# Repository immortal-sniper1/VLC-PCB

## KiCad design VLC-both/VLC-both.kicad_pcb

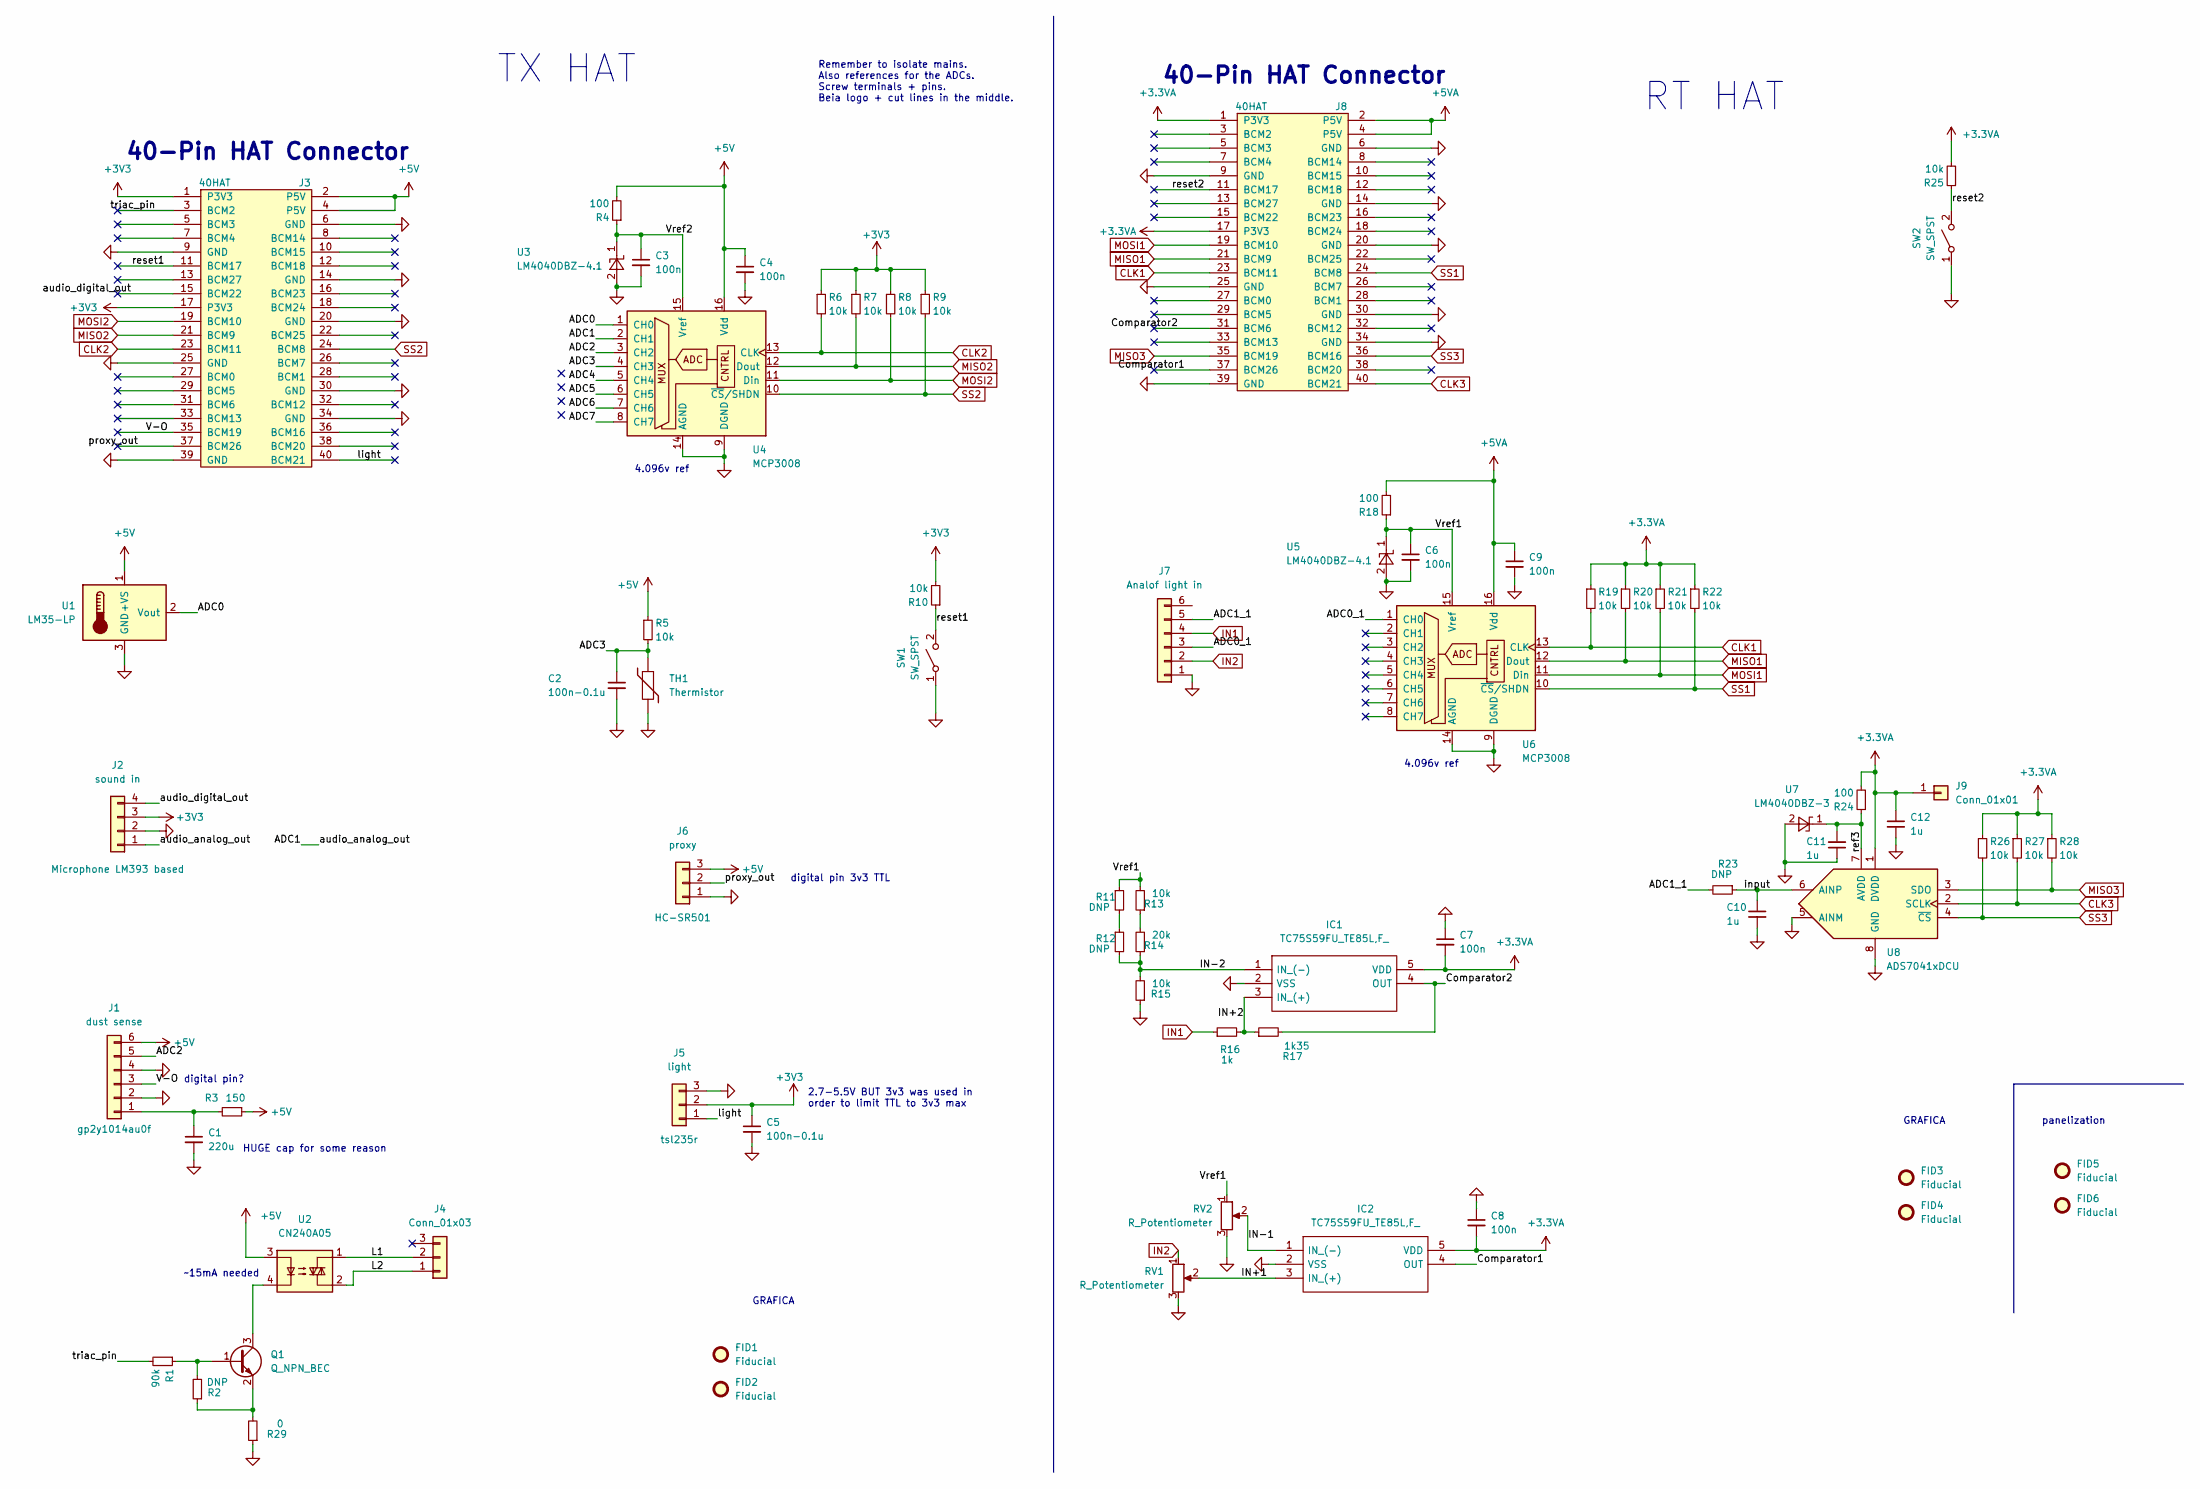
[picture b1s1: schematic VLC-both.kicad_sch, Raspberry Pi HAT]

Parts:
C1: 220u; CP_Elec_6.3x7.7
C2, C5: 100n-0.1u; C_0805_2012Metric
C3, C4, C6, C7, C8, C9: 100n; C_0805_2012Metric
C10, C11, C12: 1u; C_0805_2012Metric
FID1, FID3: Fiducial; Fiducial_0.5mm_Mask1mm
FID2, FID4: Fiducial; WEEE-Logo_4.2x6mm_SilkScreen
FID5, FID6: Fiducial; mouse bites 2.5mm wide 6mm long 0.6mm holes 0.3mm apart str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
IC1, IC2: TC75S59FU_TE85L,F_; TC75S59FUTE85LF; Mouser Part Number 757-TC75S59FUTE85LF
J1: dust sense; PinHeader_1x06_P2.54mm_Vertical
J2: sound in; PinHeader_1x04_P2.54mm_Vertical
J3, J8: 40HAT; PinSocket_2x20_P2.54mm_Vertical
J4: Conn_01x03; TerminalBlock_Altech_AK300-3_P5.00mm
J5: light; PinHeader_1x03_P2.54mm_Vertical
J6: proxy; PinHeader_1x03_P2.54mm_Vertical
J7: Analof light in; PinHeader_1x06_P2.54mm_Vertical
J9: Conn_01x01; PinHeader_1x01_P2.54mm_Vertical
Q1: Q_NPN_BEC; SOT-23
R1: 90k; R_0805_2012Metric
R2, R11, R12, R23: DNP; R_0805_2012Metric
R3: 150; R_0805_2012Metric
R4, R18, R24: 100; R_0805_2012Metric
R5, R6, R7, R8, R9, R10, R13, R15, R19, R20, R21, R22, R25, R26, R27, R28: 10k; R_0805_2012Metric
R14: 20k; R_0805_2012Metric
R16: 1k; R_0805_2012Metric
R17: 1k35; R_0805_2012Metric
R29: 0; R_0805_2012Metric
RV1, RV2: R_Potentiometer; Potentiometer_Piher_PT-6-V_Vertical
SW1, SW2: SW_SPST; PTS526SM15SMTR2LFS
TH1: Thermistor; PinHeader_1x02_P2.54mm_Vertical
U1: LM35-LP; PinHeader_1x03_P2.54mm_Vertical
U2: CN240A05; SIP4_Sharp-SSR_P7.62mm_Straight
U3, U5: LM4040DBZ-4.1; SOT-23
U4, U6: MCP3008; SOIC-16_3.9x9.9mm_P1.27mm
U7: LM4040DBZ-3; SOT-23
U8: ADS7041xDCU; VSSOP-8_2.3x2mm_P0.5mm

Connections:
+3.3VA: C7.2, C8.2, C12.1, IC1.5 (VDD), IC2.5 (VDD), J8.1 (P3V3), J8.17 (P3V3), J9.1, R19.1, R20.1, R21.1, R22.1, R24.2, R25.2, R26.1, R27.1, R28.1, U8.1 (DVDD)
+3V3: C5.1, J2.3, J3.1 (P3V3), J3.17 (P3V3), J5.2, R6.1, R7.1, R8.1, R9.1, R10.2
+5V: C4.1, J1.6, J3.2 (P5V), J3.4 (P5V), J6.3, R3.1, R4.2, R5.1, U1.1 (+VS), U2.3, U4.16 (Vdd)
+5VA: C9.1, J8.2 (P5V), J8.4 (P5V), R18.2, U6.16 (Vdd)
/ADC0: U1.2 (Vout), U4.1 (CH0)
/ADC0_1: J7.3, U6.1 (CH0)
/ADC1: J2.1, U4.2 (CH1)
/ADC1_1: J7.5, R23.2
/ADC2: J1.5, U4.3 (CH2)
/ADC3: C2.1, R5.2, TH1.1, U4.4 (CH3)
/ADC4: U4.5 (CH4)
/ADC5: U4.6 (CH5)
/ADC6: U4.7 (CH6)
/ADC7: U4.8 (CH7)
/Comparator1: IC2.4 (OUT), J8.37 (BCM26)
/Comparator2: IC1.4 (OUT), J8.31 (BCM6), R17.2
/IN+1: IC2.3 (IN_(+)), RV1.2
/IN+2: IC1.3 (IN_(+)), R16.2, R17.1
/IN-1: IC2.1 (IN_(-)), RV2.2
/IN-2: IC1.1 (IN_(-)), R12.2, R14.1, R15.2
/L1: J4.2, U2.1
/L2: J4.1, U2.2
/V-O: J1.3, J3.35 (BCM19)
/Vref1: C6.1, R11.1, R13.2, R18.1, RV2.1, U5.1 (K), U6.15 (Vref)
/Vref2: C3.1, R4.1, U3.1 (K), U4.15 (Vref)
/audio_digital_out: J2.4, J3.15 (BCM22)
/input: C10.1, R23.1, U8.6 (AINP)
/light: J3.40 (BCM21), J5.1
/proxy_out: J3.37 (BCM26), J6.2
/ref3: C11.2, R24.1, U7.1 (K), U8.7 (AVDD)
/reset1: J3.11 (BCM17), R10.1, SW1.2 (B)
/reset2: J8.11 (BCM17), R25.1, SW2.2 (B)
/triac_pin: J3.3 (BCM2), R1.2
CLK1: J8.23 (BCM11), R19.2, U6.13 (CLK)
CLK2: J3.23 (BCM11), R6.2, U4.13 (CLK)
CLK3: J8.40 (BCM21), R27.2, U8.2 (SCLK)
GND: C1.2, C2.2, C3.2, C4.2, C5.2, C6.2, C7.1, C8.1, C9.2, C10.2, C11.1, C12.2, IC1.2 (VSS), IC2.2 (VSS), J1.2, J1.4, J2.2, J3.6 (GND), J3.9 (GND), J3.14 (GND), J3.20 (GND), J3.25 (GND), J3.30 (GND), J3.34 (GND), J3.39 (GND), J5.3, J6.1, J7.1, J8.6 (GND), J8.9 (GND), J8.14 (GND), J8.20 (GND), J8.25 (GND), J8.30 (GND), J8.34 (GND), J8.39 (GND), R15.1, R29.1, RV1.3, RV2.3, SW1.1 (A), SW2.1 (A), TH1.2, U1.3 (GND), U3.2 (A), U4.9 (DGND), U4.14 (AGND), U5.2 (A), U6.9 (DGND), U6.14 (AGND), U7.2 (A), U8.5 (AINM), U8.8 (GND)
IN1: J7.4, R16.1
IN2: J7.2, RV1.1
MISO1: J8.21 (BCM9), R20.2, U6.12 (Dout)
MISO2: J3.21 (BCM9), R7.2, U4.12 (Dout)
MISO3: J8.35 (BCM19), R28.2, U8.3 (SDO)
MOSI1: J8.19 (BCM10), R21.2, U6.11 (Din)
MOSI2: J3.19 (BCM10), R8.2, U4.11 (Din)
unnamed: C1.1, J1.1, R3.2
unnamed: Q1.1 (B), R1.1, R2.2
unnamed: Q1.2 (E), R2.1, R29.2
unnamed: Q1.3 (C), U2.4
unnamed: R11.2, R12.1
unnamed: R13.1, R14.2
SS1: J8.24 (BCM8), R22.2, U6.10 (~CS/SHDN)
SS2: J3.24 (BCM8), R9.2, U4.10 (~CS/SHDN)
SS3: J8.36 (BCM16), R26.2, U8.4 (~CS)

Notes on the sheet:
4.096v ref
HUGE cap for some reason
Remember to isolate mains. Also references for the ADCs. Screw terminals + pins. Beia logo + cut lines in the middle.
40-Pin HAT Connector
~15mA needed
GRAFICA
RT HAT
2.7-5.5V BUT 3v3 was used in order to limit TTL to 3v3 max
digital pin?
digital pin 3v3 TTL
TX HAT
panelization

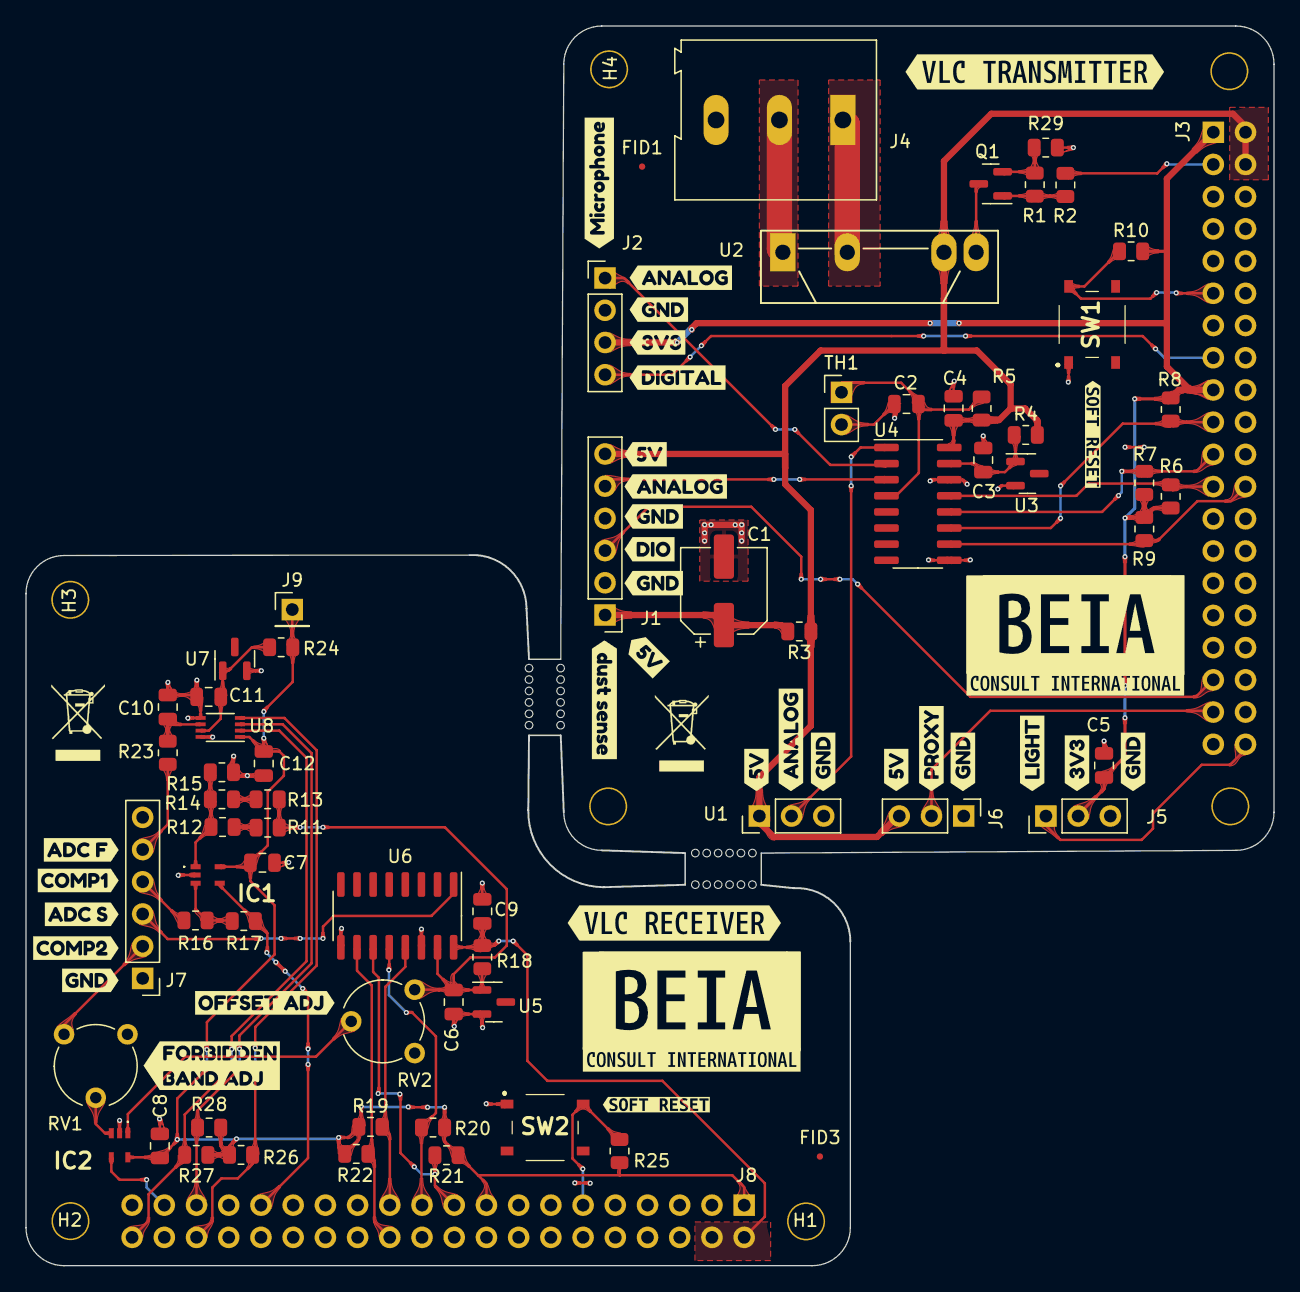
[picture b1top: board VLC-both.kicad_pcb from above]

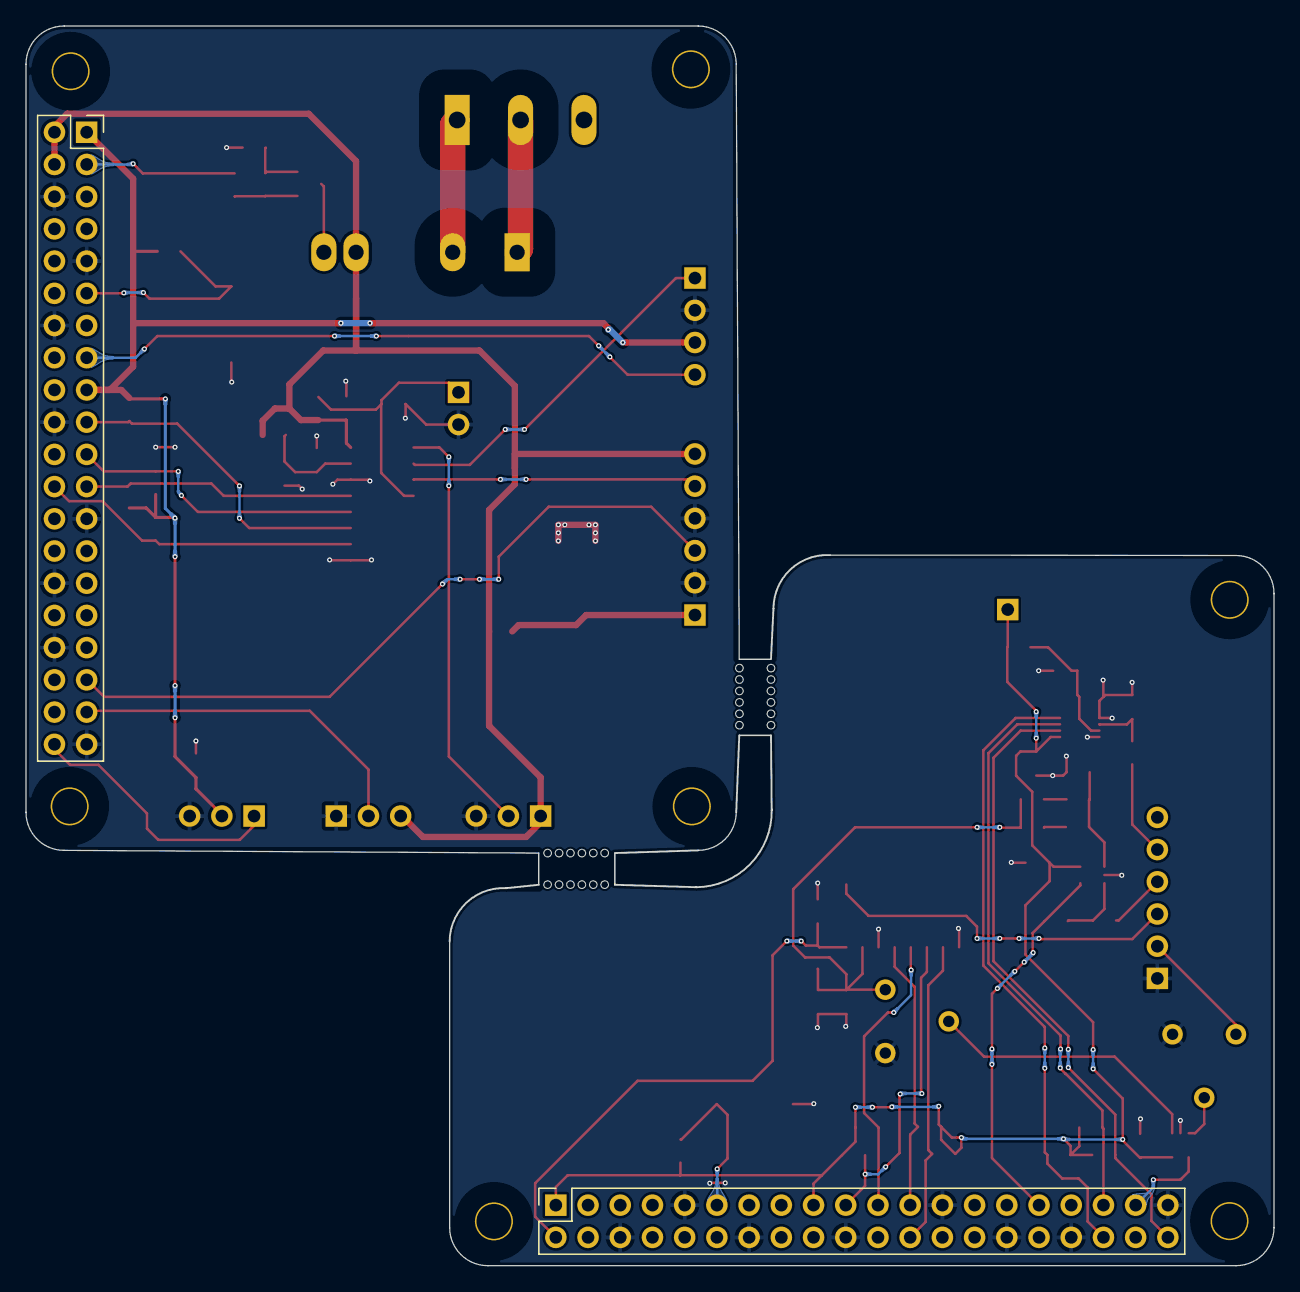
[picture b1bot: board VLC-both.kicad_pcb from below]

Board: 2 copper layers, 98.4 x 97.7 mm, 112 parts (2 on the bottom side), 49 nets.

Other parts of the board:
H1, H2, H3, H4: 3mm_Mounting_Hole; NPTH_3mm_ID
kibuzzard-62B5CDB9, kibuzzard-62B5CDB9#2: G***; kibuzzard-62B5CDB9
kibuzzard-62B56CEF, kibuzzard-62B56CEF#2, kibuzzard-62B56CEF#3, kibuzzard-62B56CEF#4: G***; kibuzzard-62B56CEF
kibuzzard-62B56DD8, kibuzzard-62B56DD8#2, kibuzzard-62B56DD8#3, kibuzzard-62B56DD8#4, kibuzzard-62B56DD8#5: G***; kibuzzard-62B56DD8
kibuzzard-62B56E37, kibuzzard-62B56E37#2, kibuzzard-62B56E37#3: G***; kibuzzard-62B56E37
kibuzzard-62B97B6B: G***; kibuzzard-62B97B6B
kibuzzard-62B97B7C: G***; kibuzzard-62B97B7C
kibuzzard-62B571D5: G***; kibuzzard-62B571D5
kibuzzard-62B594DE: G***; kibuzzard-62B594DE
kibuzzard-62B594FE: G***; kibuzzard-62B594FE
kibuzzard-62B977EB, kibuzzard-62B977EB#2: G***; kibuzzard-62B977EB
kibuzzard-62B5717A: G***; kibuzzard-62B5717A
kibuzzard-62B5718E: G***; kibuzzard-62B5718E
kibuzzard-62B5942E: G***; kibuzzard-62B5942E
kibuzzard-62B57016: G***; kibuzzard-62B57016
kibuzzard-62B57037: G***; kibuzzard-62B57037
kibuzzard-62B57048, kibuzzard-62B57048#2: G***; kibuzzard-62B57048
kibuzzard-62B57119: G***; kibuzzard-62B57119
kibuzzard-62B57254: G***; kibuzzard-62B57254
kibuzzard-62B59380: G***; kibuzzard-62B59380
kibuzzard-62B59390: G***; kibuzzard-62B59390
kibuzzard-62B59408: G***; kibuzzard-62B59408
kibuzzard-62B59413: G***; kibuzzard-62B59413
kibuzzard-62B97805, kibuzzard-62B97805#2: G***; kibuzzard-62B97805
